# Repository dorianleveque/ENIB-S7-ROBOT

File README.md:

# IHM_ProjetSEN
Projet (robot mobile) réalisé dans le cadre scolaire pour la matiere de systemes embarqués en semestre 7.

## Constitution trame CAN

* Id emmetteur (PC ou carte)
* Un premier octet de données indiquant le composant à piloter
* Un 2e octet de données pour 

## Communication par UART
Les éléments importants constituant les trames sont:
* un premier octet de données indiquant la zone du robot concernée (roues, tourelle, consigne)
* un 2e octet de données comportant la valeur 

```
void MainWindow::onSliderValueChanged(int value)
{
    qDebug()<<"Callback Slider";
    int32_t convertValue = (int32_t)value;
    int8_t poidsFort = (convertValue && 0x1111111100000000)>>8;
    int8_t poidsFaible = convertValue &&0x11111111;
    sendRobotData(ID_CONSIGNE,poidsFort,poidsFaible); // Pas besoin de les cast en char => même taille
}
```

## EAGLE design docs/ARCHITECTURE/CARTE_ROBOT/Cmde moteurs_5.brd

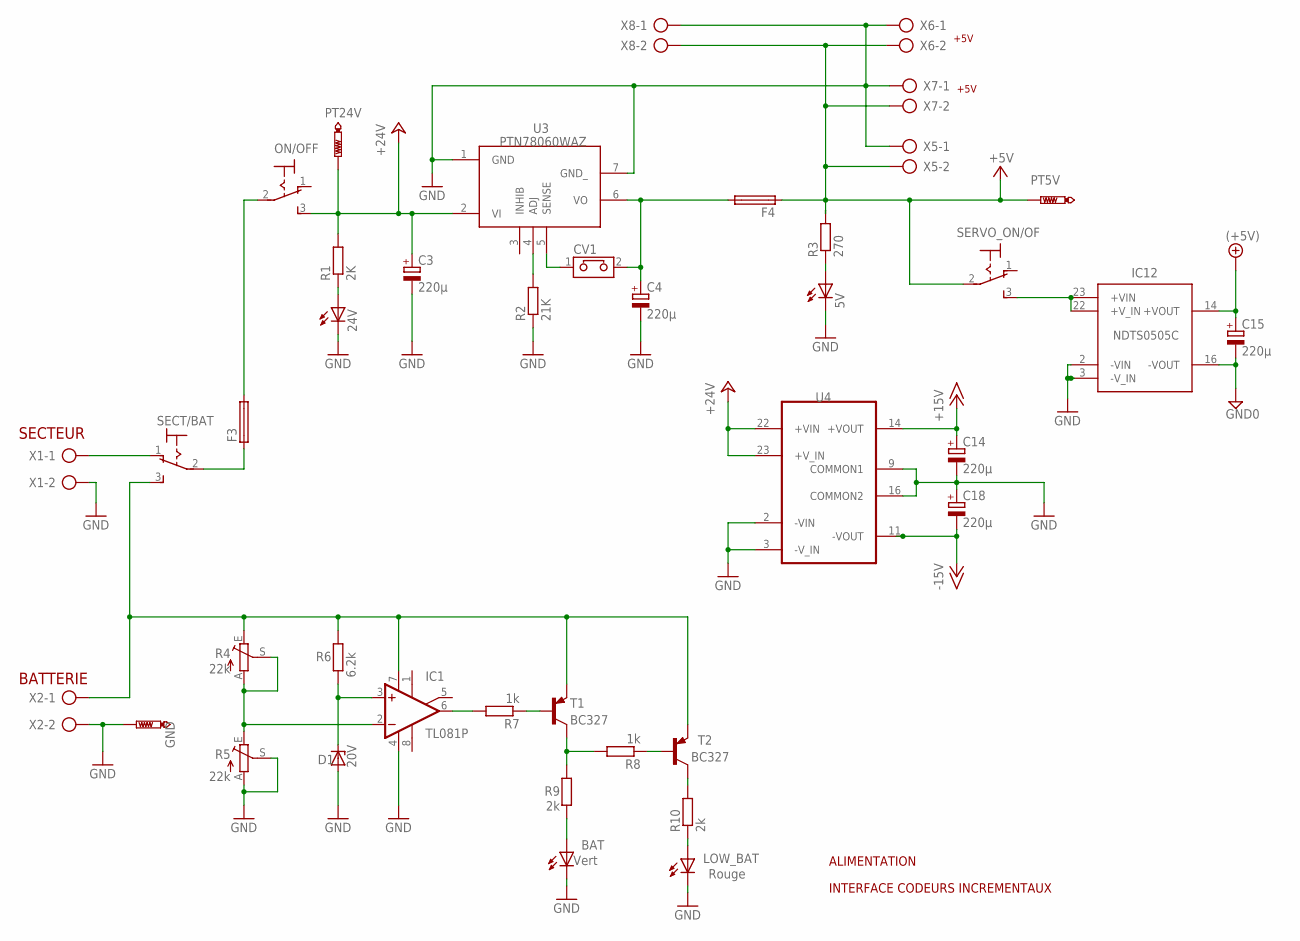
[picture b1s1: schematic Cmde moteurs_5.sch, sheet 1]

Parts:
5V, 24V: LED3MM
BAT: Vert; LED3MM
C3, C4: 220µ; E5-10,5
C14, C15, C18: 220µ; E5-8,5
CV1: CAVALIER
D1: 20V; DO34Z7
F3: SH22,5
F4: SH22,5; MPN 0031.8201
GND: PTR1PAD1-13Y; P1-13Y
IC1: TL081P; DIL08
IC12: NDTS0505C; NDTS05505
LOW_BAT: Rouge; LED3MM
ON/OFF: 320-916
PT5V, PT24V: PTR1PAD1-13Y; P1-13Y
R1: 2K; 0207/10
R2: 21K; 0207/10
R3: 270; 0207/10
R4, R5: 22k; B64Y
R6: 6.2k; 0207/10
R7, R8: 1k; 0207/10
R9, R10: 2k; 0207/10
SECT/BAT: 320-916
SERVO_ON/OF: 320-916
T1, T2: BC327; TO92-EBC
U3: PTN78060WAD; PTN78060
U4: TEN8-2423; NDTS05505
X1, X2, X5, X6, X7, X8: AK300/2

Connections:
+5V: C15.+, F4.1, IC12.14 (+VOUT), PT5V.TP, R3.2, SERVO_ON/OF.2, X5.2, X6.2, X7.2, X8.2; also elsewhere on the board
+15V: C14.+, U4.14 (+VOUT); also elsewhere on the board
+24V: C3.+, ON/OFF.3 (S), PT24V.TP, R1.2, U3.2 (VI), U4.22 (+VIN), U4.23 (+V_IN); also elsewhere on the board
-15V: C18.-, U4.11 (-VOUT); also elsewhere on the board
GND: 5V.K (C), 24V.K (C), BAT.K (C), C3.-, C4.-, C14.-, C15.-, C18.+, D1.A, GND.TP, IC1.4 (V-), IC12.2 (-VIN), IC12.3 (-V_IN), IC12.16 (-VOUT), LOW_BAT.K (C), R2.1, R5.A, R5.S, U3.1 (GND), U3.7 (GND_), U4.2 (-VIN), U4.3 (-V_IN), U4.9 (COMMON1), U4.16 (COMMON2), X1.2, X2.2, X5.1, X6.1, X7.1, X8.1; also elsewhere on the board
unnamed: IC1.7 (V+), R4.E, R6.2, SECT/BAT.3 (S), T1.E, T2.E, X2.1
unnamed: F3.1, SECT/BAT.2
unnamed: F3.2, ON/OFF.2
unnamed: R2.2, U3.4 (ADJ)
unnamed: 24V.A, R1.1
unnamed: 5V.A, R3.1
unnamed: CV1.1, U3.5 (SENSE)
unnamed: D1.C, IC1.3 (+IN), R6.1
unnamed: IC1.2 (-IN), R4.A, R4.S, R5.E
unnamed: IC1.6 (OUT), R7.2
unnamed: R7.1, T1.B
unnamed: R8.1, T2.B
unnamed: R8.2, R9.2, T1.C
unnamed: BAT.A, R9.1
unnamed: LOW_BAT.A, R10.1
unnamed: R10.2, T2.C
unnamed: IC12.22 (+V_IN), IC12.23 (+VIN), SERVO_ON/OF.3 (S)
unnamed: C4.+, CV1.2, F4.2, U3.6 (VO)
unnamed: SECT/BAT.1 (O), X1.1

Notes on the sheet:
ALIMENTATION
INTERFACE CODEURS INCREMENTAUX
SECTEUR
BATTERIE
+5V
PTN78060WAZ

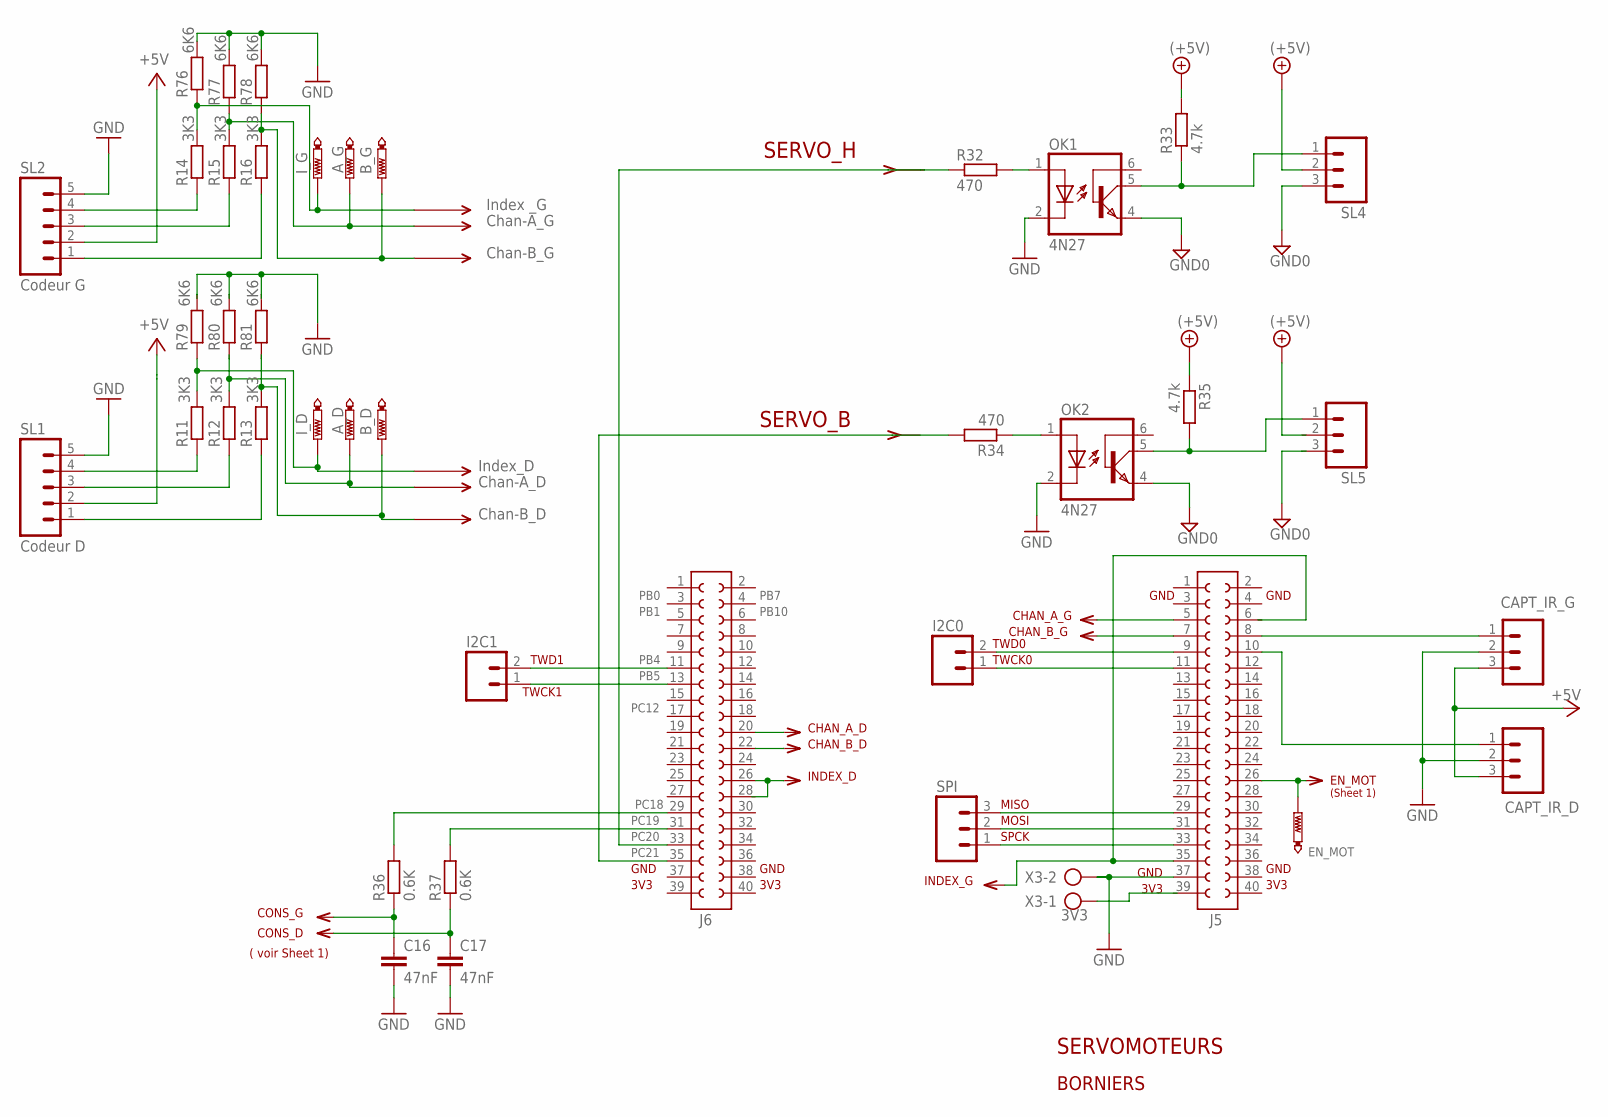
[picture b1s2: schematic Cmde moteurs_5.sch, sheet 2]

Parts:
A_D: PTR1PAD1-13Y; P1-13Y
A_G: PTR1PAD1-13Y; P1-13Y
B_D: PTR1PAD1-13Y; P1-13Y
B_G: PTR1PAD1-13Y; P1-13Y
C16, C17: 47nF; C050-025X075
CAPT_IR_D: M03; 03P
CAPT_IR_G: M03; 03P
EN_MOT: PTR1PAD1-13Y; P1-13Y
I2C0, I2C1: M02; 02P
I_D: PTR1PAD1-13Y; P1-13Y
I_G: PTR1PAD1-13Y; P1-13Y
J5, J6: CON_FE20-2_ROBOT; CON_FE20-2
OK1, OK2: 4N27; DIL06
R11, R12, R13, R14, R15, R16: 3K3; 0207/10
R32, R34: 470; 0207/10
R33, R35: 4.7k; 0207/10
R36, R37: 0.6K; 0207/10
R76, R77, R78, R79, R80, R81: 6K6; 0207/10
SL1: Codeur D; 05P
SL2: Codeur G; 05P
SL4, SL5: M03; 03P
SPI: M03; 03P
X3: 3V3; AK300/2

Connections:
+5V: CAPT_IR_D.3, CAPT_IR_G.3, R33.2, R35.1, SL1.2, SL2.2, SL4.2; also elsewhere on the board
GND: C16.2, C17.2, CAPT_IR_D.2, CAPT_IR_G.2, J5.37, OK1.2 (C), OK1.4 (EMI), OK2.2 (C), OK2.4 (EMI), R76.2, R77.2, R78.2, R79.2, R80.2, R81.2, SL1.5, SL2.5, SL4.3, SL5.3, X3.2; also elsewhere on the board
unnamed: R11.1, SL1.4
unnamed: R12.1, SL1.3
unnamed: R13.1, SL1.1
unnamed: R14.1, SL2.4
unnamed: R15.1, SL2.3
unnamed: R16.1, SL2.1
unnamed: OK1.1 (A), R32.2
unnamed: OK1.5 (COL), R33.1, SL4.1
unnamed: OK2.5 (COL), R35.2, SL5.1
unnamed: OK2.1 (A), R34.1
unnamed: I2C0.2, J5.9
unnamed: I2C0.1, J5.11
unnamed: J6.29, R36.2
unnamed: J6.31, R37.2
unnamed: C17.1, R37.1
unnamed: C16.1, R36.1
unnamed: J6.33, R32.1
unnamed: J6.35, R34.2
unnamed: I2C1.2, J6.11
unnamed: I2C1.1, J6.13
unnamed: J5.33, SPI.1
unnamed: J5.31, SPI.2
unnamed: J5.29, SPI.3
unnamed: CAPT_IR_G.1, J5.8
unnamed: CAPT_IR_D.1, J5.10
unnamed: EN_MOT.TP, J5.26
unnamed: B_D.TP, R13.2, R81.1
unnamed: B_G.TP, R16.2, R78.1
unnamed: A_D.TP, R12.2, R80.1
unnamed: I_G.TP, R14.2, R76.1
unnamed: A_G.TP, R15.2, R77.1
unnamed: I_D.TP, R11.2, R79.1

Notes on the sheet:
SERVOMOTEURS
SERVO_H
SERVO_B
PB0
PB1
PB4
PB5
PC12
PC18
PC19
PC20
PC21
GND
3V3
INDEX_D
CHAN_B_D
CHAN_A_D
PB7
PB10
CONS_G
CONS_D
( voir Sheet 1)
TWD1
TWCK1
CHAN_A_G
CHAN_B_G
TWD0
TWCK0
MISO
MOSI
SPCK
INDEX_G
BORNIERS
EN_MOT
(Sheet 1)
Index _G
Chan-A_G
Chan-B_G
Index_D
Chan-A_D

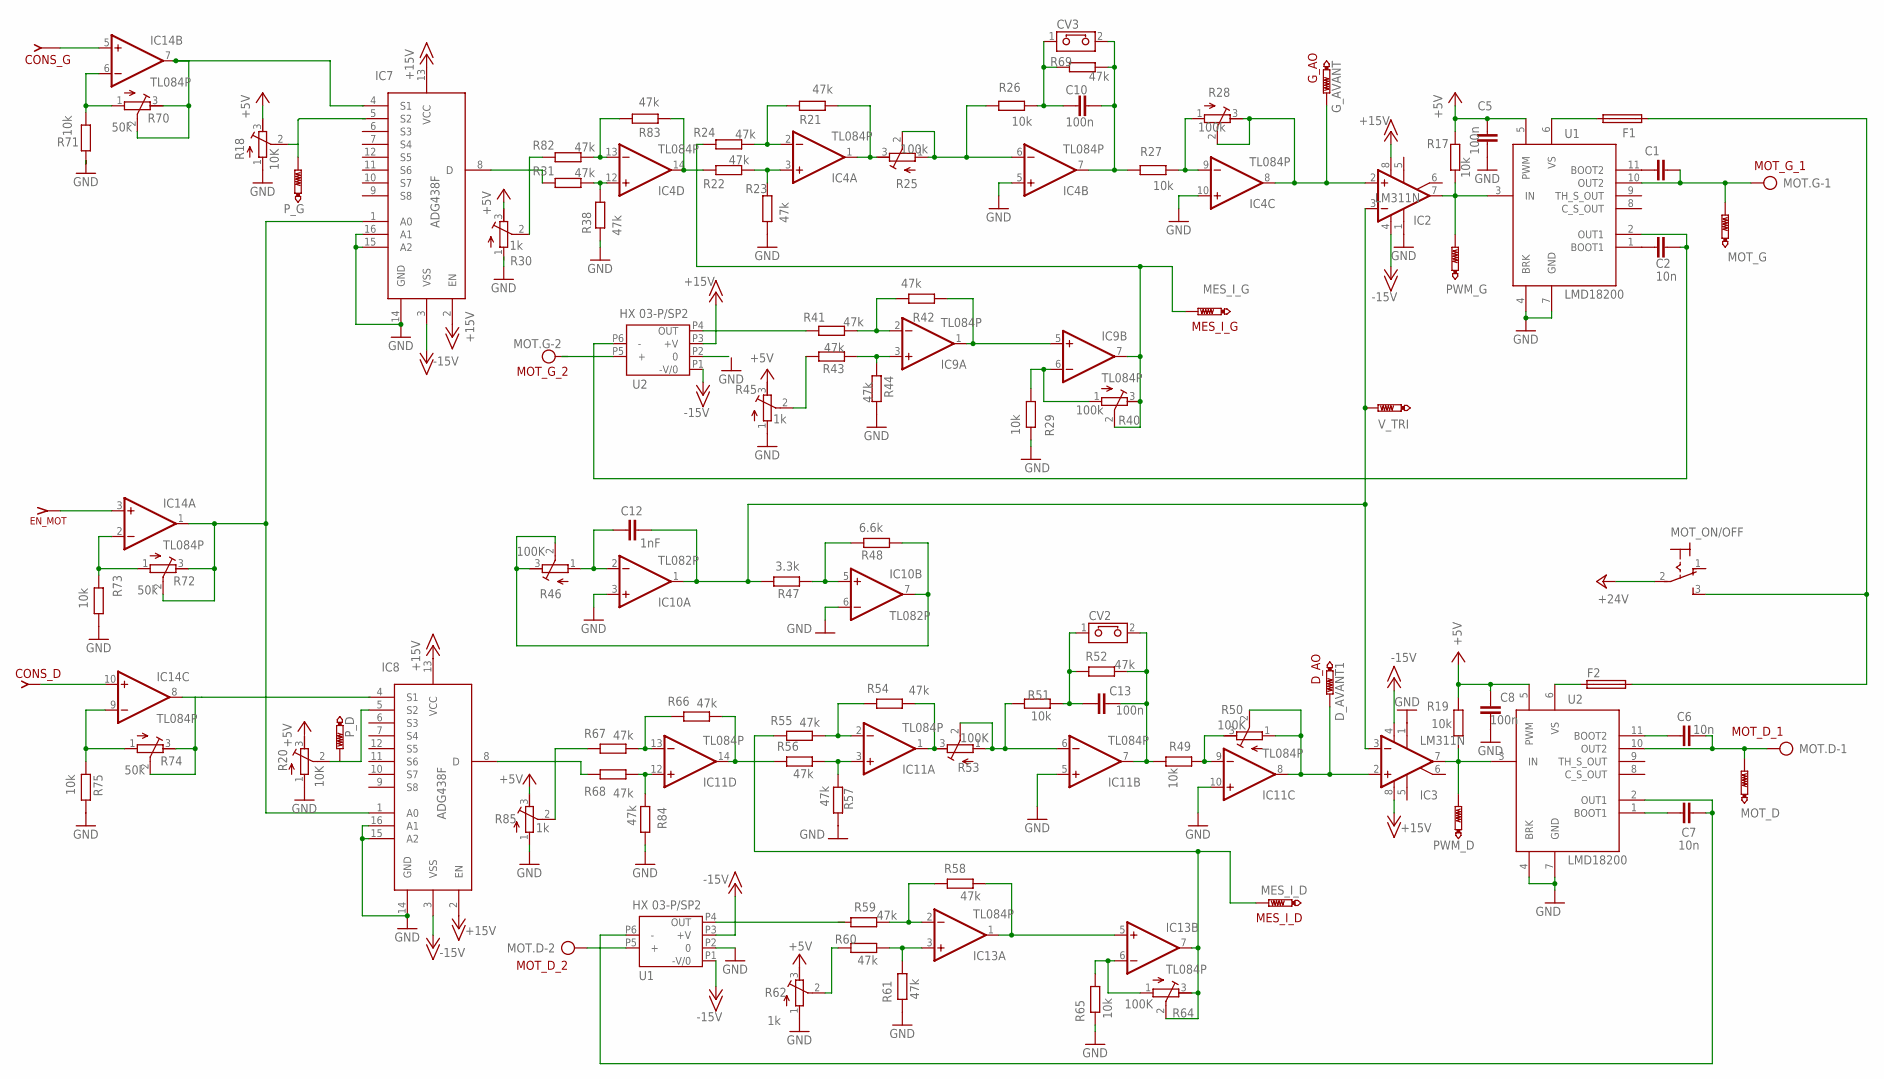
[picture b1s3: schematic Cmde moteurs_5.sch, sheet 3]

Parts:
C1, C2, C6, C7: 10n; C050-025X075
C5, C8, C10, C13: 100n; C050-025X075
C12: 1nF; C050-025X075
CV2, CV3: CAVALIER
D_AVANT1: PTR1PAD1-13Y; P1-13Y
F1, F2: SH22,5
G_AVANT: PTR1PAD1-13Y; P1-13Y
IC2, IC3: LM311N; DIL08
IC4, IC9, IC11, IC13, IC14: TL084P; DIL14
IC7, IC8: ADG438F; DIL16
IC10: TL082P; DIL08
MES_I_D: PTR1PAD1-13Y; P1-13Y
MES_I_G: PTR1PAD1-13Y; P1-13Y
MOT.D, MOT.G: AK300/2
MOT_D: PTR1PAD1-13Y; P1-13Y
MOT_G: PTR1PAD1-13Y; P1-13Y
MOT_ON/OFF: 320-916
PWM_D: PTR1PAD1-13Y; P1-13Y
PWM_G: PTR1PAD1-13Y; P1-13Y
P_D: PTR1PAD1-13Y; P1-13Y
P_G: PTR1PAD1-13Y; P1-13Y
R17, R19, R26, R27, R29, R49, R51, R65, R71, R73, R75: 10k; 0207/10
R18, R20: 10K; RTRIM3296W
R21, R22, R23, R24, R31, R38, R41, R42, R43, R44, R52, R54, R55, R56, R57, R58, R59, R60, R61, R66, R67, R68, R69, R82, R83, R84: 47k; 0207/10
R25, R28, R40: 100k; RTRIM3296W
R30, R45, R62, R85: 1k; RTRIM3296W
R46, R50, R53, R64: 100K; RTRIM3296W
R47: 3.3k; 0207/10
R48: 6.6k; 0207/10
R70, R72, R74: 50k; RTRIM3296W
U1, U2: LMD18200; MULTIWATT_11
U$1, U$2: HX03
V_TRI: V_TRI; P1-13Y

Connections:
+5V: C5.2, C8.2, R17.2, R18.3 (E), R19.2, R30.3 (E), R45.3 (E), R62.3 (E), R85.3 (E), U1.5 (PWM), U2.5 (PWM); also elsewhere on the board
+15V: IC2.8 (V+), IC3.8 (V+), IC7.2 (EN), IC7.13 (VCC), IC8.2 (EN), IC8.13 (VCC), U$2.P3 (+V); also elsewhere on the board
+24V: MOT_ON/OFF.2; also elsewhere on the board
-15V: IC2.4 (V-), IC3.4 (V-), IC7.3 (VSS), IC8.3 (VSS), U$1.P1 (-V/0), U$1.P3 (+V), U$2.P1 (-V/0); also elsewhere on the board
GND: C5.1, C8.1, IC2.1 (GND), IC3.1 (GND), IC4.5 (+IN), IC4.10 (+IN), IC7.14 (GND), IC7.15 (A2), IC7.16 (A1), IC8.14 (GND), IC8.15 (A2), IC8.16 (A1), IC10.3 (+IN), IC10.6 (-IN), IC11.5 (+IN), IC11.10 (+IN), R18.1 (A), R20.1 (A), R23.1, R29.1, R38.1, R44.1, R45.1 (A), R57.2, R61.2, R62.1 (A), R65.2, R71.1, R73.1, R75.1, R84.2, R85.1 (A), U1.4 (BRK), U1.7 (GND), U2.4 (BRK), U2.7 (GND), U$1.P2 (0); also elsewhere on the board
unnamed: F1.1, U1.6 (VS)
unnamed: C1.1, U1.11 (BOOT2)
unnamed: C1.2, MOT.G.1, MOT_G.TP, U1.10 (OUT2)
unnamed: IC14.7 (OUT), R70.2 (S), R70.3 (E)
unnamed: IC11.1 (OUT), R53.3 (E), R54.1
unnamed: IC7.8 (D), R31.2
unnamed: IC2.7 (OUT), PWM_G.TP, R17.1, U1.3 (IN)
unnamed: IC4.3 (+IN), R22.1, R23.2
unnamed: C2.2, U1.1 (BOOT1)
unnamed: F2.1, U2.6 (VS)
unnamed: C6.1, U2.11 (BOOT2)
unnamed: C6.2, MOT.D.1, MOT_D.TP, U2.10 (OUT2)
unnamed: IC3.7 (OUT), PWM_D.TP, R19.1, U2.3 (IN)
unnamed: C13.2, CV2.1, R51.1, R52.2
unnamed: P_D.TP, R20.2 (S)
unnamed: C7.2, U2.1 (BOOT1)
unnamed: IC14.6 (-IN), R70.1 (A), R71.2
unnamed: F1.2, F2.2, MOT_ON/OFF.3 (S)
unnamed: IC14.8 (OUT), R74.2 (S), R74.3 (E)
unnamed: C7.1, U2.2 (OUT1), U$1.P6 (-)
unnamed: MOT.D.2, U$1.P5 (+)
unnamed: IC4.1 (OUT), R21.1, R25.3 (E)
unnamed: IC13.1 (OUT), IC13.5 (+IN), R58.1
unnamed: IC4.2 (-IN), R21.2, R24.1
unnamed: IC4.6 (-IN), R25.1 (A), R25.2 (S), R26.2
unnamed: C10.1, CV3.1, R26.1, R69.2
unnamed: C13.1, CV2.2, IC11.7 (OUT), R49.2, R52.1
unnamed: C10.2, CV3.2, IC4.7 (OUT), R27.2, R69.1
unnamed: IC4.9 (-IN), R27.1, R28.1 (A)
unnamed: R41.1, U$2.P4 (OUT)
unnamed: IC11.9 (-IN), R49.1, R50.3 (E)
unnamed: G_AVANT.TP, IC2.2 (+IN), IC4.8 (OUT), R28.2 (S), R28.3 (E)
unnamed: IC9.6 (-IN), R29.2, R40.1 (A)
unnamed: IC9.3 (+IN), R43.2, R44.2
unnamed: IC9.2 (-IN), R41.2, R42.1
unnamed: C2.1, U1.2 (OUT1), U$2.P6 (-)
unnamed: D_AVANT1.TP, IC3.2 (+IN), IC11.8 (OUT), R50.1 (A), R50.2 (S)
unnamed: IC11.6 (-IN), R51.2, R53.1 (A), R53.2 (S)
unnamed: P_G.TP, R18.2 (S)
unnamed: R43.1, R45.2 (S)
unnamed: IC9.7 (OUT), MES_I_G.TP, R24.2, R40.2 (S), R40.3 (E)
unnamed: IC4.13 (-IN), R82.1, R83.2
unnamed: R30.2 (S), R82.2
unnamed: IC11.14 (OUT), R56.2, R66.1
unnamed: IC4.12 (+IN), R31.1, R38.2
unnamed: R60.2, R62.2 (S)
unnamed: IC13.6 (-IN), R64.1 (A), R65.1
unnamed: IC13.7 (OUT), MES_I_D.TP, R55.2, R64.2 (S), R64.3 (E)
unnamed: IC4.14 (OUT), R22.2, R83.1
unnamed: IC11.13 (-IN), R66.2, R67.1
unnamed: IC11.12 (+IN), R68.1, R84.1
unnamed: R67.2, R85.2 (S)
unnamed: IC8.8 (D), R68.2
unnamed: IC9.1 (OUT), IC9.5 (+IN), R42.2
unnamed: C12.2, IC10.2 (-IN), R46.1 (A)
unnamed: C12.1, IC2.3 (-IN), IC3.3 (-IN), IC10.1 (OUT), R47.1, V_TRI.TP
unnamed: IC10.5 (+IN), R47.2, R48.1
unnamed: IC10.7 (OUT), R46.2 (S), R46.3 (E), R48.2
unnamed: IC11.3 (+IN), R56.1, R57.1
unnamed: IC11.2 (-IN), R54.2, R55.1
unnamed: IC13.3 (+IN), R60.1, R61.1
unnamed: IC13.2 (-IN), R58.2, R59.1
unnamed: IC14.2 (-IN), R72.1 (A), R73.2
unnamed: IC14.9 (-IN), R74.1 (A), R75.2
unnamed: IC7.1 (A0), IC8.1 (A0), IC14.1 (OUT), R72.2 (S), R72.3 (E)
V+: IC4.4 (V+), IC9.4 (V+), IC10.8 (V+), IC11.4 (V+), IC13.4 (V+), IC14.4 (V+)
V-: IC4.11 (V-), IC9.11 (V-), IC10.4 (V-), IC11.11 (V-), IC13.11 (V-), IC14.11 (V-)

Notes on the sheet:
MES_I_G
MOT_G_1
MOT_G_2
CONS_G
EN_MOT
MES_I_D
MOT_D_1
CONS_D
MOT_D_2
HX 03-P/SP2
G_AO
D_AO

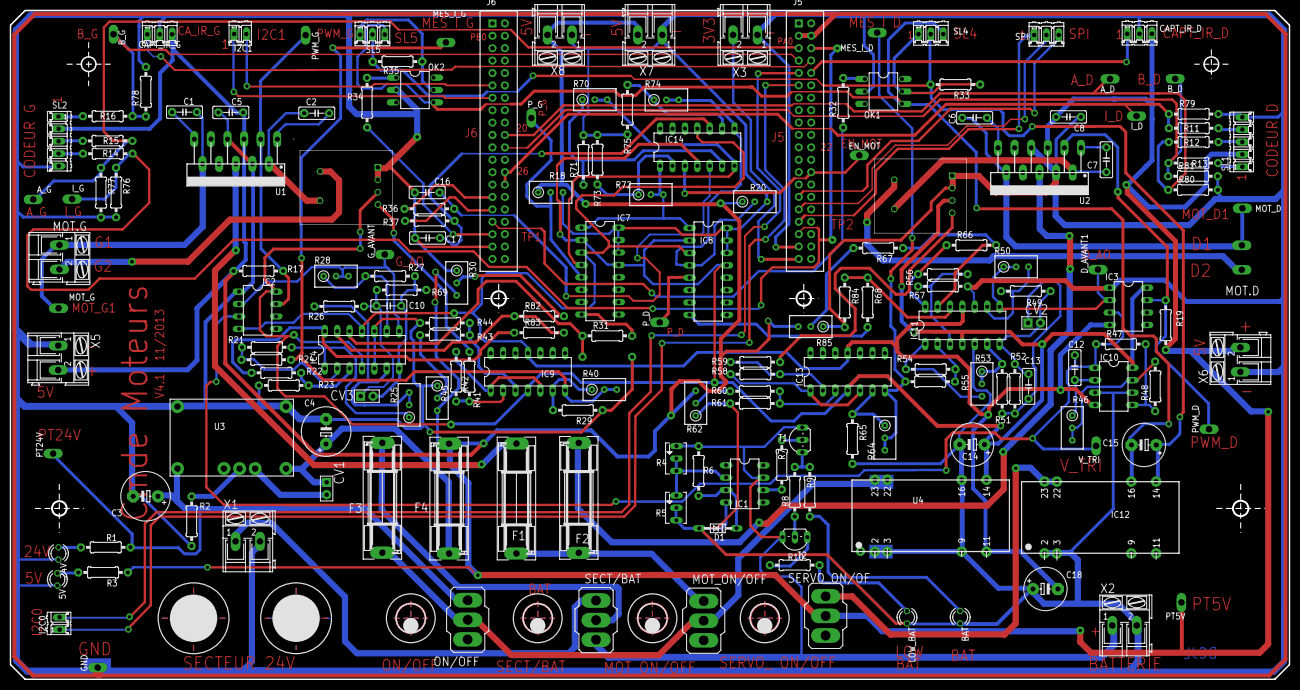
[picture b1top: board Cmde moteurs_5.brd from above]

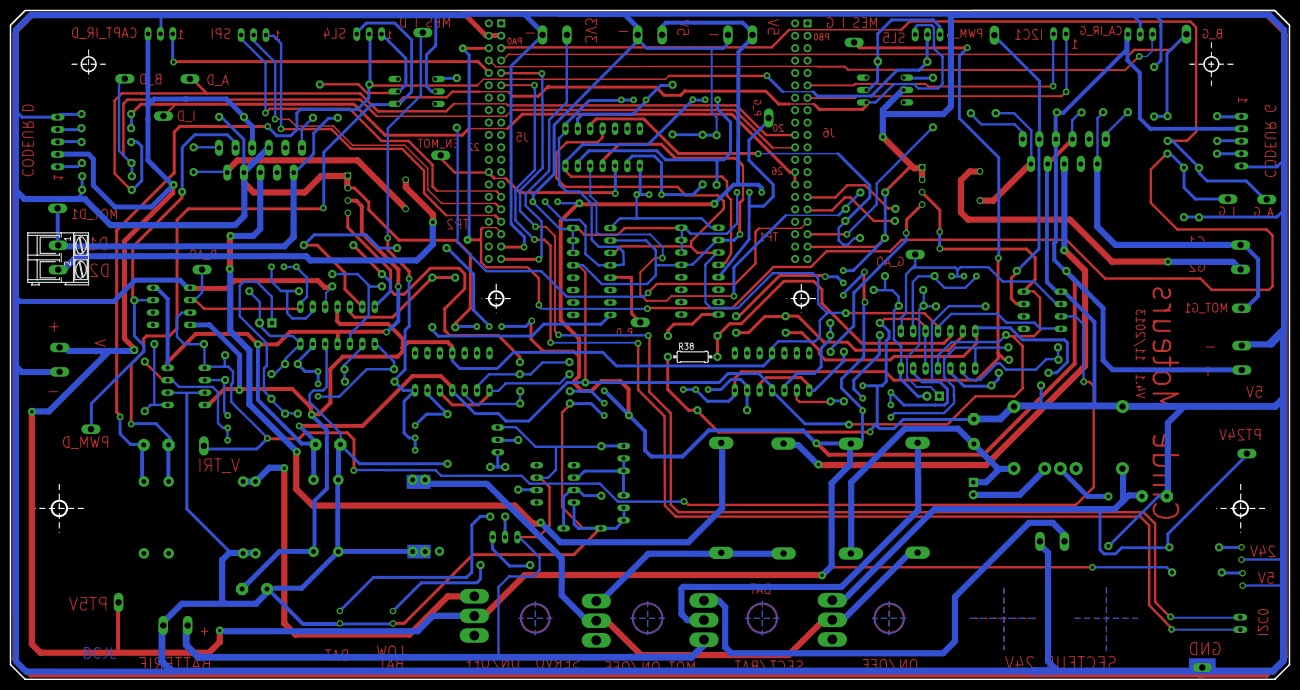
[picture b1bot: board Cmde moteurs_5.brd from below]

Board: 2 copper layers, 262.0 x 137.0 mm, 178 parts (2 on the bottom side), 123 nets.

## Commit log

2019-05-17 Creation du projet
2019-05-17 Event clavier
2019-05-20 new organisation
2019-05-20 new new
2019-05-20 Mise a jour IHM version ecole
2019-05-20 avancement 20/05
2019-05-27 Mise à jour 27/05
2019-05-29 add some changes
2019-05-29 remove robot code
2019-05-29 remove again robot code
2019-05-29 add robot code
2019-05-29 resolve ?
2019-05-29 nop resolve => remove code robot
2019-05-29 add robot code => problem resolved
2019-06-03 hey !
2019-06-03 test fonctionnel zigbee
2019-06-17 commit before merge
2019-06-17 add asservissement pour les 2 moteurs
2019-06-17 begin multi-task and get all sensors
2019-06-17 Interface complete sans test
2019-06-19 before separating branches
2019-06-19 target cam fonctionnelle + début multi-tâches
2019-06-19 2e putain de commit
2019-06-20 multi-task
2019-06-21 Multi-task fonctionnel
2019-06-21 ajout de la correction du glissement + affichage du mode selectionnné
2019-06-21 new commit
2019-06-22 code refactoring
2019-06-22 fix motor speed problem
2019-06-24 mode auto
2021-03-22 add docs
